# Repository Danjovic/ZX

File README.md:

# Sinclair ZX Computer Projects 

## Tek AVR
Tek is a ZX Spectrum keyboard emulator based on an AVR microcontroller and some glue logic chips.
It works by converting the PS/2 keystrokes into a bitmap representation of the keyboard matrix and updating its outputs with the corresponding keys pressed depending on the state of lines A8..A15 each time the Z80 reads the port 0xFE.
The circuit is heavilly based on ATMega88 but any Arduino with enough pins should do it. 
Development documented in my personal blog at the months of 
[april](http://danjovic.blogspot.com/2014/04) 
[may](http://danjovic.blogspot.com/2014/05) 
[june](http://danjovic.blogspot.com/2014/06) 
[july](http://danjovic.blogspot.com/2014/07) 
[august](http://danjovic.blogspot.com/2014/08) 
, 2014.

## Tek
Generic matrix keyboard emulator. Based on PIC 16F688 can be compiled on SDCC or in CCS C.  [Hackaday.io project page](https://hackaday.io/project/6140-tek-ps2-to-matrix-keyboard-adapteremulator)

## Tek V2
Provides quick and dirty matrix keyboard emulator to complement ZX-80/81 and ZX Spectrum boards.  [Hackaday.io project page](https://hackaday.io/project/166917-tek-v2)

## paddle
Adapter for using Sega Master System [HPD-200](https://segaretro.org/Paddle_Control) paddle controller with [Kempston] (https://en.wikipedia.org/wiki/Kempston_Interface) interface. 
Test programs are provided for ZX81 and Speccy. [Hackaday.io page](https://hackaday.io/page/6399-sms-paddles-on-sinclair-zx-computers)

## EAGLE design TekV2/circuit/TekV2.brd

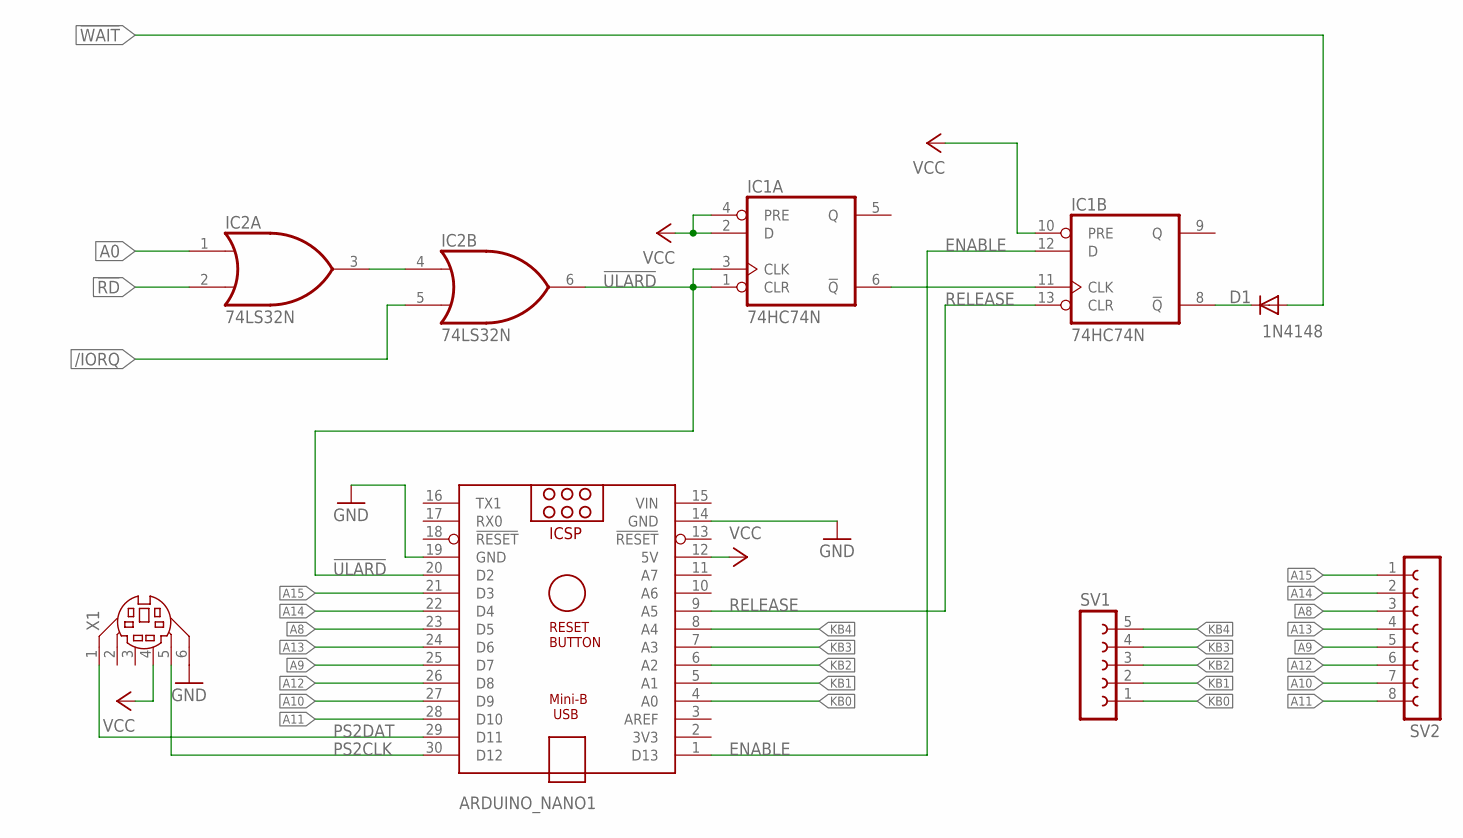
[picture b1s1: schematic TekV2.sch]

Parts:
ARDUINO_NANO1: ARDUINO_NANO
D1: 1N4148; DO35-7
IC1: 74HC74N; DIL14
IC2: 74LS32N; DIL14
SV1: FE05-1
SV2: FE08-1; FE08
X1: MDIN06K

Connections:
!RD: IC2.2 (I1)
!ULARD: ARDUINO_NANO1.20 (D2), IC1.1 (CLR), IC1.3 (CLK), IC2.6 (O)
!WAIT: D1.A
/IORQ: IC2.5 (I1)
A0: IC2.1 (I0)
A8: ARDUINO_NANO1.23 (D5), SV2.3
A9: ARDUINO_NANO1.25 (D7), SV2.5
A10: ARDUINO_NANO1.27 (D9), SV2.7
A11: ARDUINO_NANO1.28 (D10), SV2.8
A12: ARDUINO_NANO1.26 (D8), SV2.6
A13: ARDUINO_NANO1.24 (D6), SV2.4
A14: ARDUINO_NANO1.22 (D4), SV2.2
A15: ARDUINO_NANO1.21 (D3), SV2.1
ENABLE: ARDUINO_NANO1.1 (D13), IC1.12 (D)
GND: ARDUINO_NANO1.14 (GND), ARDUINO_NANO1.19 (GND), IC1.7 (GND), IC2.7 (GND), X1.6
KB0: ARDUINO_NANO1.4 (A0), SV1.1
KB1: ARDUINO_NANO1.5 (A1), SV1.2
KB2: ARDUINO_NANO1.6 (A2), SV1.3
KB3: ARDUINO_NANO1.7 (A3), SV1.4
KB4: ARDUINO_NANO1.8 (A4), SV1.5
unnamed: IC1.6 (!Q), IC1.11 (CLK)
unnamed: D1.C, IC1.8 (!Q)
unnamed: IC2.3 (O), IC2.4 (I0)
PS2CLK: ARDUINO_NANO1.30 (D12), X1.5
PS2DAT: ARDUINO_NANO1.29 (D11), X1.1
RELEASE: ARDUINO_NANO1.9 (A5), IC1.13 (CLR)
VCC: ARDUINO_NANO1.12 (5V), IC1.2 (D), IC1.4 (PRE), IC1.10 (PRE), IC1.14 (VCC), IC2.14 (VCC), X1.4
VIN: ARDUINO_NANO1.15 (VIN)

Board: 2 copper layers, 7 parts (0 on the bottom side), 23 nets, no tracks yet.

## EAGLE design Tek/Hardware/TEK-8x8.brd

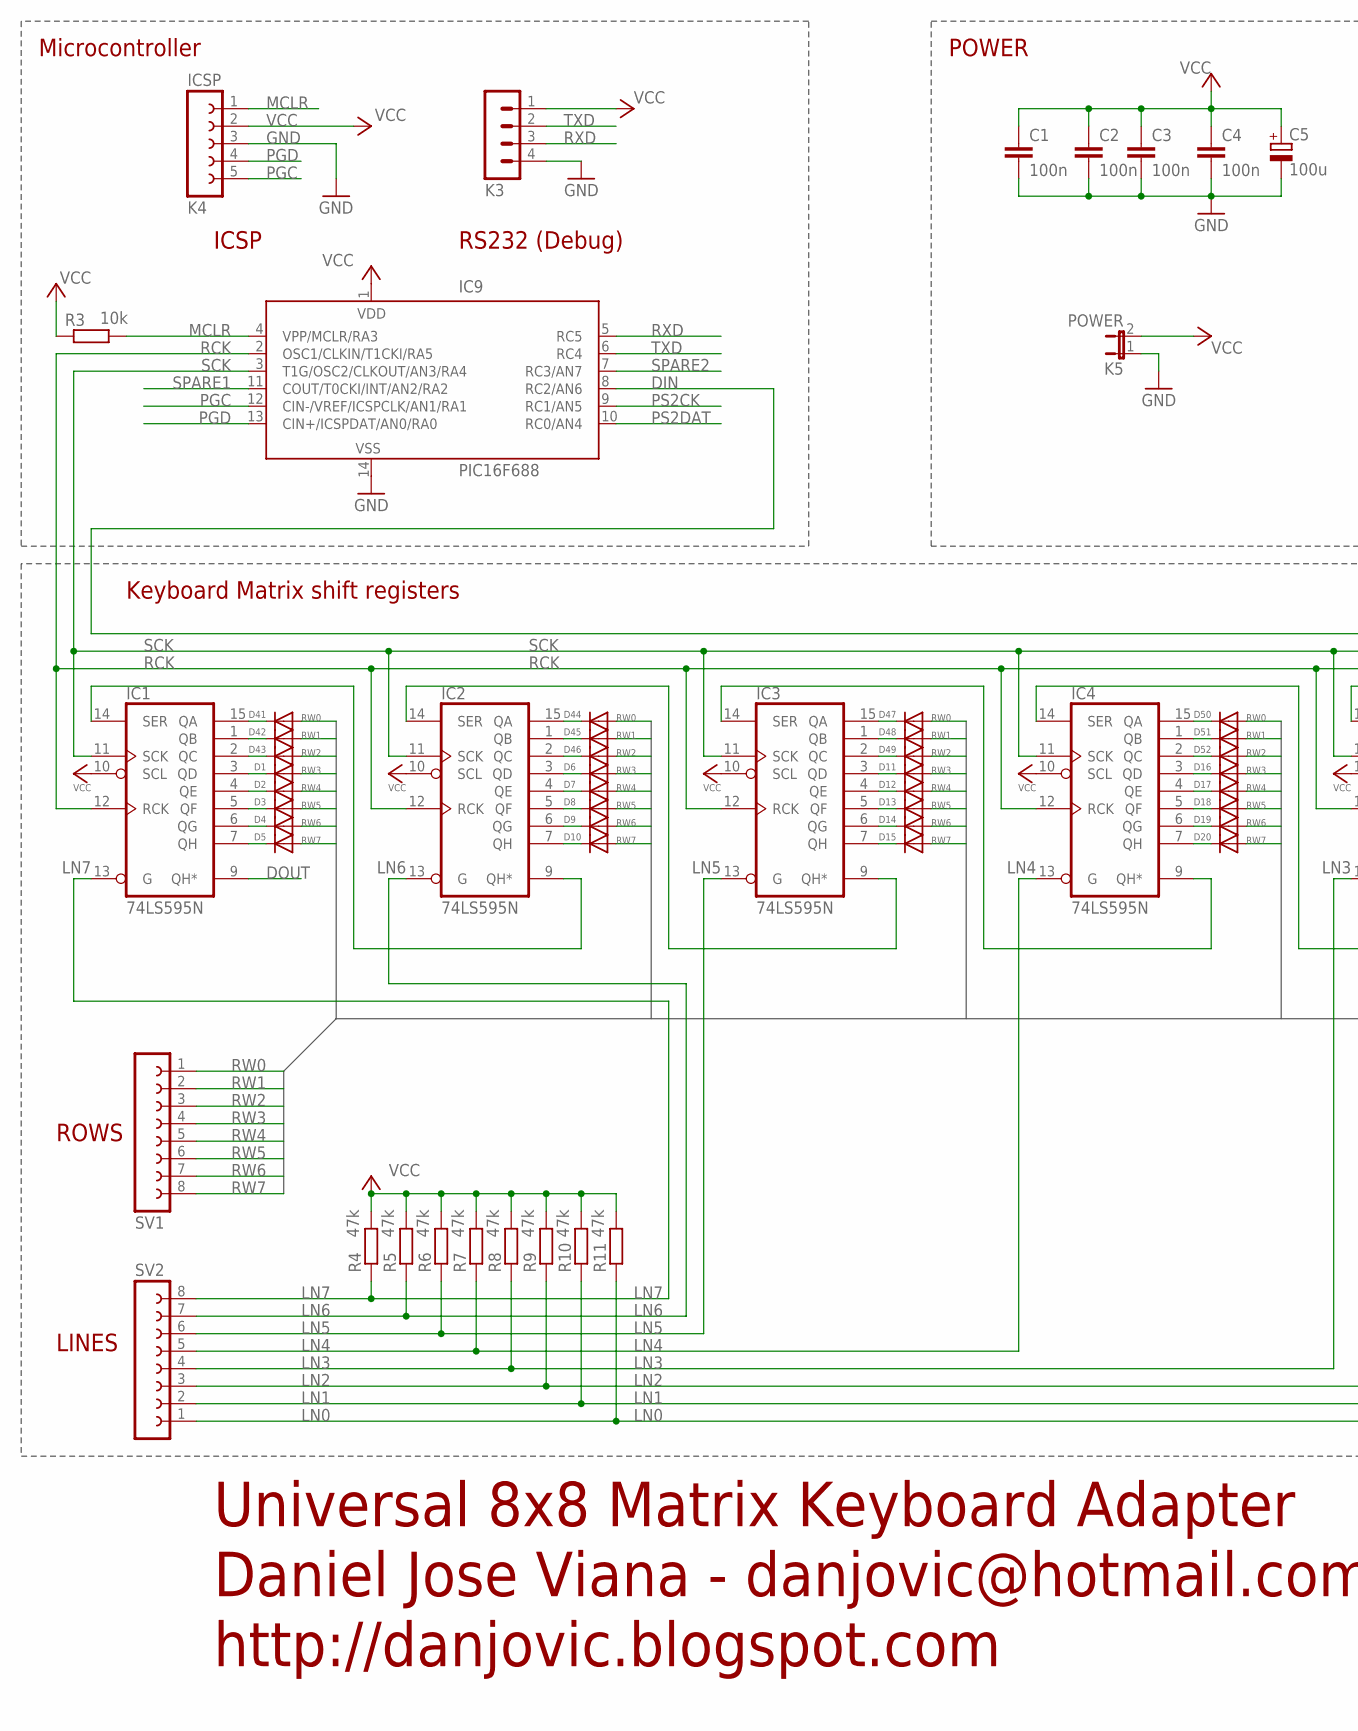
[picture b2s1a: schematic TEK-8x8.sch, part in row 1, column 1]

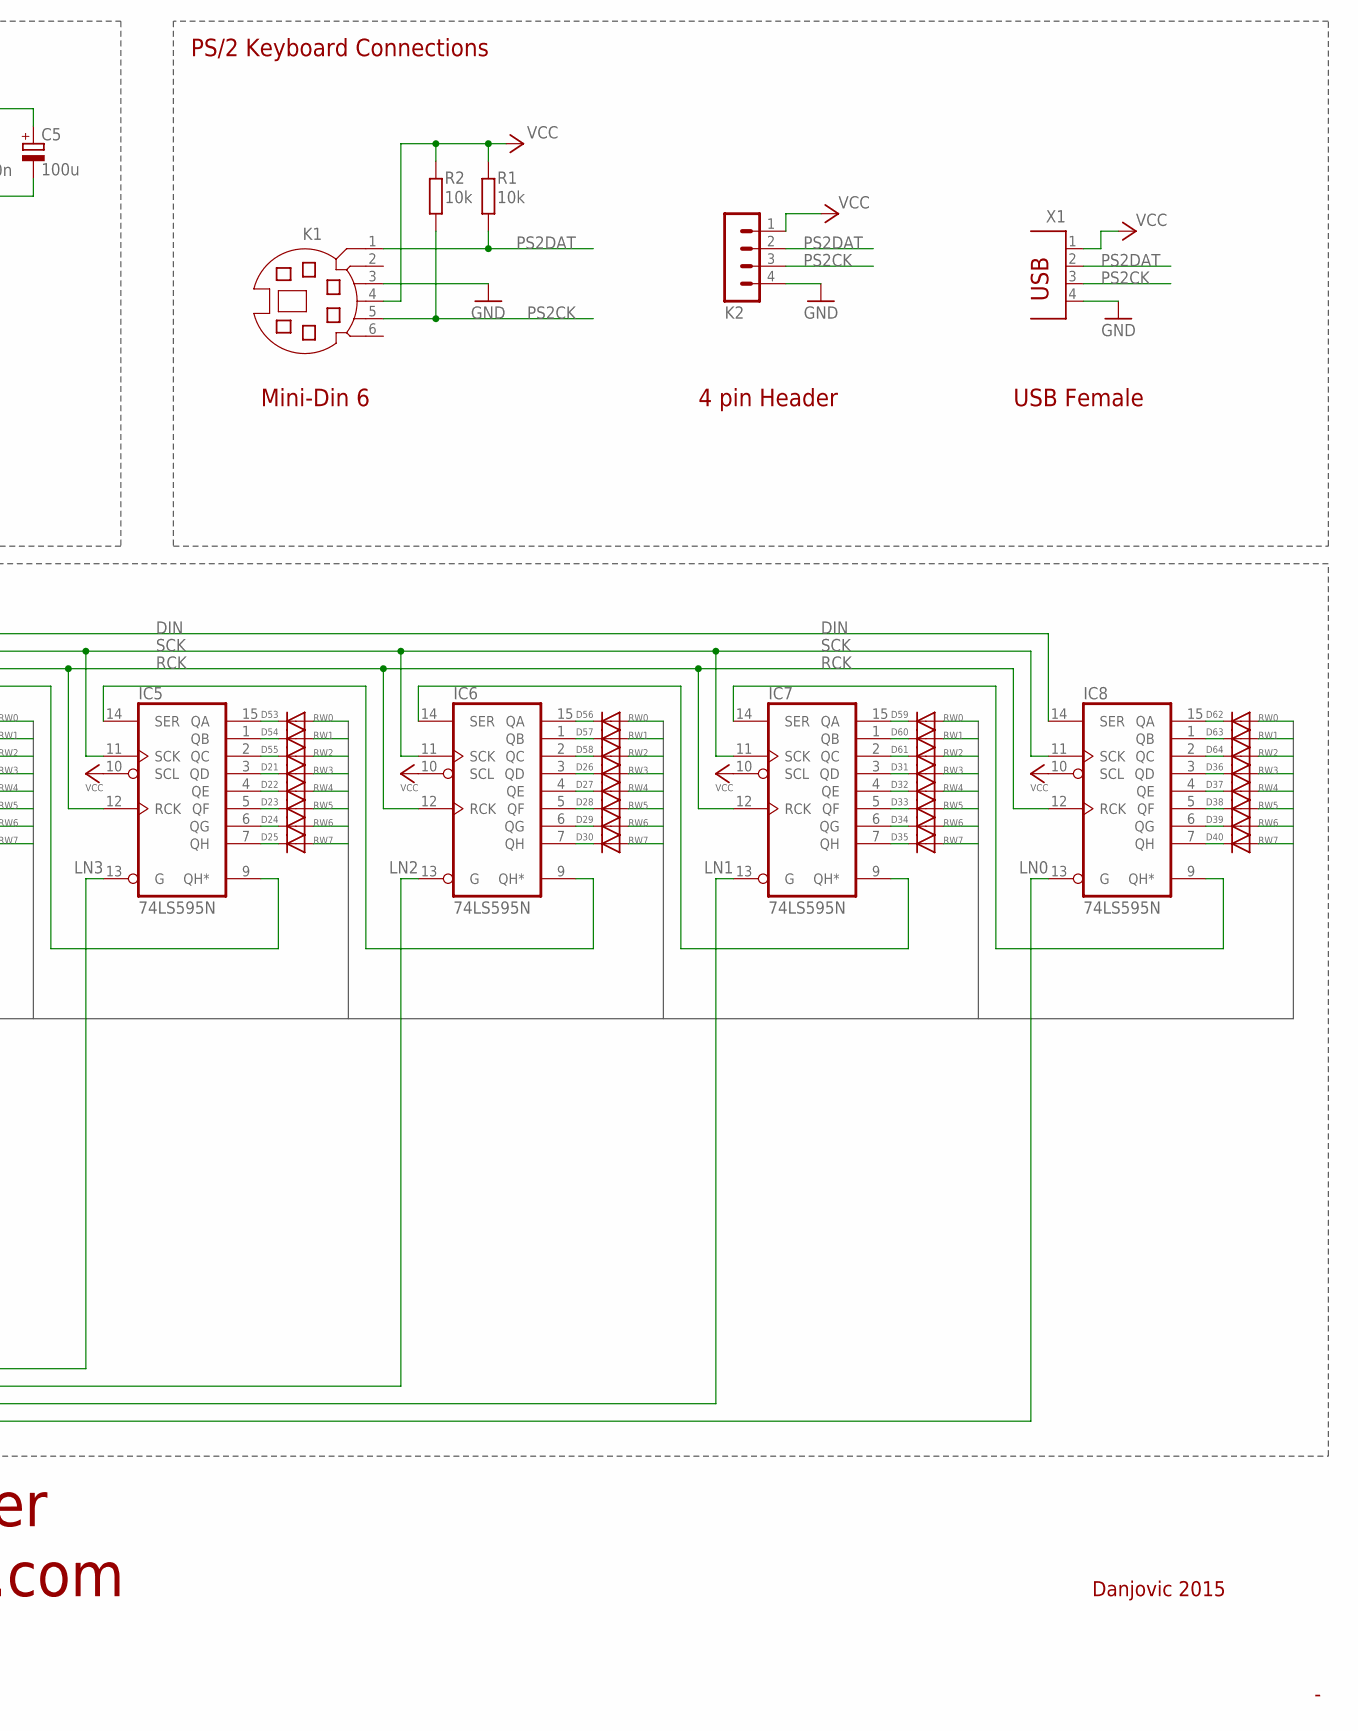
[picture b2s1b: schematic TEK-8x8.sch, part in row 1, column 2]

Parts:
C1, C2, C3, C4: 100n; C050-030X075
C5: 100u; E3,5-10
D1, D2, D3, D4, D5, D6, D7, D8, D9, D10, D11, D12, D13, D14, D15, D16, D17, D18, D19, D20, D21, D22, D23, D24, D25, D26, D27, D28, D29, D30, D31, D32, D33, D34, D35, D36, D37, D38, D39, D40, D41, D42, D43, D44, D45, D46, D47, D48, D49, D50, D51, D52, D53, D54, D55, D56, D57, D58, D59, D60, D61, D62, D63, D64: DIODE-D-2.5; D-2.5
IC1, IC2, IC3, IC4, IC5, IC6, IC7, IC8: 74LS595N; DIL16
IC9: PIC16F688; DIL14
K1: MD06SS; MDIN06SS
K2, K3: MA04-1
K4: ICSP; FE05-1
K5: POWER; JP1
R1, R2, R3: 10k; 0204/7
R4, R5, R6, R7, R8, R9, R10, R11: 47k; 0204/7
SV1, SV2: FE08-1; FE08
X1: PN87520

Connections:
DIN: IC8.14 (SER), IC9.8 (RC2/AN6)
DOUT: IC1.9 (QH*)
GND: C1.2, C2.2, C3.2, C4.2, C5.-, IC1.8 (GND), IC2.8 (GND), IC3.8 (GND), IC4.8 (GND), IC5.8 (GND), IC6.8 (GND), IC7.8 (GND), IC8.8 (GND), IC9.14 (VSS), K1.3, K2.4, K3.4, K4.3, K5.1, X1.4
LN0: IC8.13 (G), R11.1, SV2.1
LN1: IC7.13 (G), R10.1, SV2.2
LN2: IC6.13 (G), R9.1, SV2.3
LN3: IC5.13 (G), R8.1, SV2.4
LN4: IC4.13 (G), R7.1, SV2.5
LN5: IC3.13 (G), R6.1, SV2.6
LN6: IC2.13 (G), R5.1, SV2.7
LN7: IC1.13 (G), R4.1, SV2.8
MCLR: IC9.4 (VPP/MCLR/RA3), K4.1, R3.1
unnamed: D62.C, IC8.15 (QA)
unnamed: D36.C, IC8.3 (QD)
unnamed: D37.C, IC8.4 (QE)
unnamed: D38.C, IC8.5 (QF)
unnamed: D39.C, IC8.6 (QG)
unnamed: D40.C, IC8.7 (QH)
unnamed: D31.C, IC7.3 (QD)
unnamed: D32.C, IC7.4 (QE)
unnamed: D33.C, IC7.5 (QF)
unnamed: D34.C, IC7.6 (QG)
unnamed: D35.C, IC7.7 (QH)
unnamed: IC1.14 (SER), IC2.9 (QH*)
unnamed: D26.C, IC6.3 (QD)
unnamed: D27.C, IC6.4 (QE)
unnamed: D28.C, IC6.5 (QF)
unnamed: IC4.14 (SER), IC5.9 (QH*)
unnamed: D29.C, IC6.6 (QG)
unnamed: IC2.14 (SER), IC3.9 (QH*)
unnamed: D30.C, IC6.7 (QH)
unnamed: D21.C, IC5.3 (QD)
unnamed: D22.C, IC5.4 (QE)
unnamed: D23.C, IC5.5 (QF)
unnamed: IC5.14 (SER), IC6.9 (QH*)
unnamed: D24.C, IC5.6 (QG)
unnamed: D25.C, IC5.7 (QH)
unnamed: D16.C, IC4.3 (QD)
unnamed: D17.C, IC4.4 (QE)
unnamed: D18.C, IC4.5 (QF)
unnamed: IC3.14 (SER), IC4.9 (QH*)
unnamed: D19.C, IC4.6 (QG)
unnamed: D20.C, IC4.7 (QH)
unnamed: D11.C, IC3.3 (QD)
unnamed: D12.C, IC3.4 (QE)
unnamed: D13.C, IC3.5 (QF)
unnamed: D14.C, IC3.6 (QG)
unnamed: D15.C, IC3.7 (QH)
unnamed: D6.C, IC2.3 (QD)
unnamed: D7.C, IC2.4 (QE)
unnamed: D8.C, IC2.5 (QF)
unnamed: D9.C, IC2.6 (QG)
unnamed: D10.C, IC2.7 (QH)
unnamed: D1.C, IC1.3 (QD)
unnamed: D2.C, IC1.4 (QE)
unnamed: IC6.14 (SER), IC7.9 (QH*)
unnamed: D3.C, IC1.5 (QF)
unnamed: D4.C, IC1.6 (QG)
unnamed: D5.C, IC1.7 (QH)
unnamed: D63.C, IC8.1 (QB)
unnamed: IC7.14 (SER), IC8.9 (QH*)
unnamed: D64.C, IC8.2 (QC)
unnamed: D59.C, IC7.15 (QA)
unnamed: D60.C, IC7.1 (QB)
unnamed: D61.C, IC7.2 (QC)
unnamed: D56.C, IC6.15 (QA)
unnamed: D57.C, IC6.1 (QB)
unnamed: D58.C, IC6.2 (QC)
unnamed: D53.C, IC5.15 (QA)
unnamed: D54.C, IC5.1 (QB)
unnamed: D55.C, IC5.2 (QC)
unnamed: D50.C, IC4.15 (QA)
unnamed: D51.C, IC4.1 (QB)
unnamed: D52.C, IC4.2 (QC)
unnamed: D44.C, IC2.15 (QA)
unnamed: D45.C, IC2.1 (QB)
unnamed: D46.C, IC2.2 (QC)
unnamed: D41.C, IC1.15 (QA)
unnamed: D42.C, IC1.1 (QB)
unnamed: D43.C, IC1.2 (QC)
unnamed: D47.C, IC3.15 (QA)
unnamed: D48.C, IC3.1 (QB)
unnamed: D49.C, IC3.2 (QC)
PGC: IC9.12 (CIN-/VREF/ICSPCLK/AN1/RA1), K4.5
PGD: IC9.13 (CIN+/ICSPDAT/AN0/RA0), K4.4
PS2CK: IC9.9 (RC1/AN5), K1.5, K2.3, R2.1, X1.3
PS2DAT: IC9.10 (RC0/AN4), K1.1, K2.2, R1.1, X1.2
RCK: IC1.12 (RCK), IC2.12 (RCK), IC3.12 (RCK), IC4.12 (RCK), IC5.12 (RCK), IC6.12 (RCK), IC7.12 (RCK), IC8.12 (RCK), IC9.2 (OSC1/CLKIN/T1CKI/RA5)
RW0: D41.A, D44.A, D47.A, D50.A, D53.A, D56.A, D59.A, D62.A, SV1.1
RW1: D42.A, D45.A, D48.A, D51.A, D54.A, D57.A, D60.A, D63.A, SV1.2
RW2: D43.A, D46.A, D49.A, D52.A, D55.A, D58.A, D61.A, D64.A, SV1.3
RW3: D1.A, D6.A, D11.A, D16.A, D21.A, D26.A, D31.A, D36.A, SV1.4
RW4: D2.A, D7.A, D12.A, D17.A, D22.A, D27.A, D32.A, D37.A, SV1.5
RW5: D3.A, D8.A, D13.A, D18.A, D23.A, D28.A, D33.A, D38.A, SV1.6
RW6: D4.A, D9.A, D14.A, D19.A, D24.A, D29.A, D34.A, D39.A, SV1.7
RW7: D5.A, D10.A, D15.A, D20.A, D25.A, D30.A, D35.A, D40.A, SV1.8
RXD: IC9.5 (RC5), K3.3
SCK: IC1.11 (SCK), IC2.11 (SCK), IC3.11 (SCK), IC4.11 (SCK), IC5.11 (SCK), IC6.11 (SCK), IC7.11 (SCK), IC8.11 (SCK), IC9.3 (T1G/OSC2/CLKOUT/AN3/RA4)
SPARE1: IC9.11 (COUT/T0CKI/INT/AN2/RA2)
SPARE2: IC9.7 (RC3/AN7)
TXD: IC9.6 (RC4), K3.2
VCC: C1.1, C2.1, C3.1, C4.1, C5.+, IC1.10 (SCL), IC1.16 (VCC), IC2.10 (SCL), IC2.16 (VCC), IC3.10 (SCL), IC3.16 (VCC), IC4.10 (SCL), IC4.16 (VCC), IC5.10 (SCL), IC5.16 (VCC), IC6.10 (SCL), IC6.16 (VCC), IC7.10 (SCL), IC7.16 (VCC), IC8.10 (SCL), IC8.16 (VCC), IC9.1 (VDD), K1.4, K2.1, K3.1, K4.2, K5.2, R1.2, R2.2, R3.2, R4.2, R5.2, R6.2, R7.2, R8.2, R9.2, R10.2, R11.2, X1.1

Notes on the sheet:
Danjovic 2015
Universal 8x8 Matrix Keyboard Adapter
Daniel Jose Viana - danjovic@hotmail.com
http://danjovic.blogspot.com
PS/2 Keyboard Connections
Mini-Din 6
4 pin Header
USB Female
RS232 (Debug)
ICSP
ROWS
LINES
POWER
Microcontroller
Keyboard Matrix shift registers

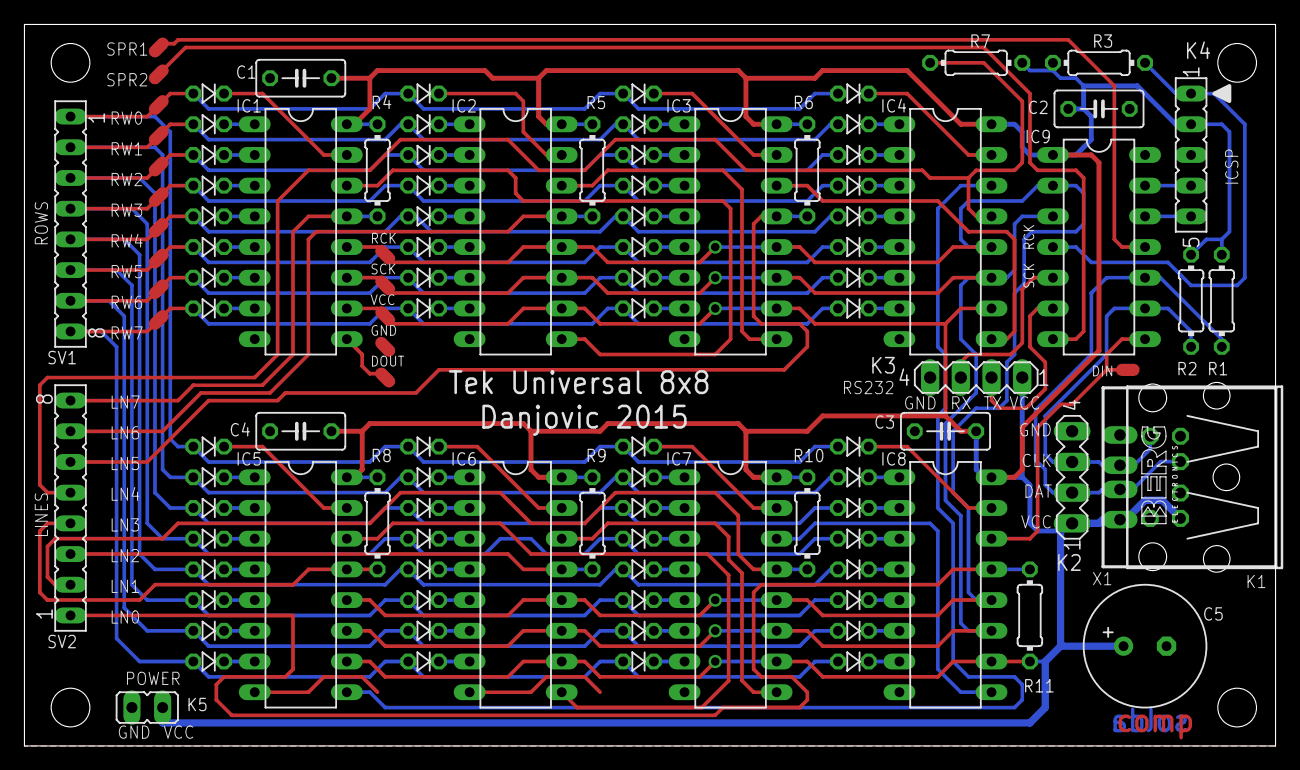
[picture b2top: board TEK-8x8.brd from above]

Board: 2 copper layers, 103.5 x 59.7 mm, 97 parts (0 on the bottom side), 99 nets.

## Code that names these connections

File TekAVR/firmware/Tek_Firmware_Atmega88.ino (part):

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
 * 
 *                       +--___--+ 
 *               RESET --|1    28|-- PC5 RELEASE to WAIT generator
 *              RX PD0 --|2    27|-- PC4 DD0 to LS367
 *              TX PD1 --|3    26|-- PC3 DD1 to LS367  
 *     INT0 /ULARD PD2 --|4    25|-- PC2 DD2 to LS367 
 *     INT1 PS2CLK PD3 --|5    24|-- PC1 DD3 to LS367    
 *          PS2DAT PD4 --|6    23|-- PC0 DD4 to LS367         
 *     Shift Clock VCC --|7    22|-- GND            
 *                 GND --|8    21|-- AREF         
 *           XTAL1 PB6 --|9    20|-- AVCC       
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*/
#define Pin_PS2_DAT 4  // PD4 is Arduino Digital 4
#define Pin_PS2_CLK 3  // PD3 is Arduino Digital 3
//#define Pin_RELEASE 19 // PC5 is Arduino Digital 19 (Analog 5) 

const int Pin_RELEASE=19;

#define Pin_Z80_A8  8  // PB0 is Arduino Digital 8
#define Pin_Z80_A9  9  // PB1 is Arduino Digital 9
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
void Pulse_RELEASE()
{
  digitalWrite(Pin_RELEASE, LOW);
  asm ("nop");  
  asm ("nop");  
  asm ("nop");  
  asm ("nop");  
  digitalWrite(Pin_RELEASE, HIGH); 
}


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    
   :: "I" (_SFR_IO_ADDR(PINB)), "I" (_SFR_IO_ADDR(PIND)) , "I" (_SFR_IO_ADDR(PORTC)) ); 
  
  digitalWrite(Pin_RELEASE, LOW);
  asm volatile ("nop");  
  digitalWrite(Pin_RELEASE, HIGH); 
  
}
  
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  DDRC = 0x3F ; // all pins from port C as outputs 
  PORTC = 0x3F; // initialize all pins from PORT C in HIGH level
 
  pinMode(Pin_RELEASE, OUTPUT);
  //digitalWrite(Pin_RELEASE,HIGH);
  
  Pulse_RELEASE();
  Clear_Matrix(); 
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
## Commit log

2019-07-23 Added ZX81 paddle test
2019-08-05 Added Tek V2 project
2019-08-05 Created project TekV2
2019-08-24 Added Tek (v1) project
2019-10-02 alfa release, so far functional
2019-10-08 Intermediary upload, Added option to generate code to ZX81 and Speccy, bugged
    Added option to generate code to ZX81 and Speccy, still bugged.
2019-10-09 fixed keyboard matrix mapping
2019-10-11 wip, simple upload
2019-10-12 beta release
2020-02-01 Enhanced makefile. Works both on Windows and Linux.
2020-02-01 cleanup
2020-09-18 Uploaded Tek AVR project
2020-09-18 Upload of files
2022-11-27 fixed connection of diode
2023-04-25 Added casts to avoid SDCC warnings on implicit type conversion
